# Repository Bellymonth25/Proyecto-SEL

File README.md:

# Proyecto-SEL
Proyecto del desarrollo de una PCB de un filtro paso bajas de 8vo orden.

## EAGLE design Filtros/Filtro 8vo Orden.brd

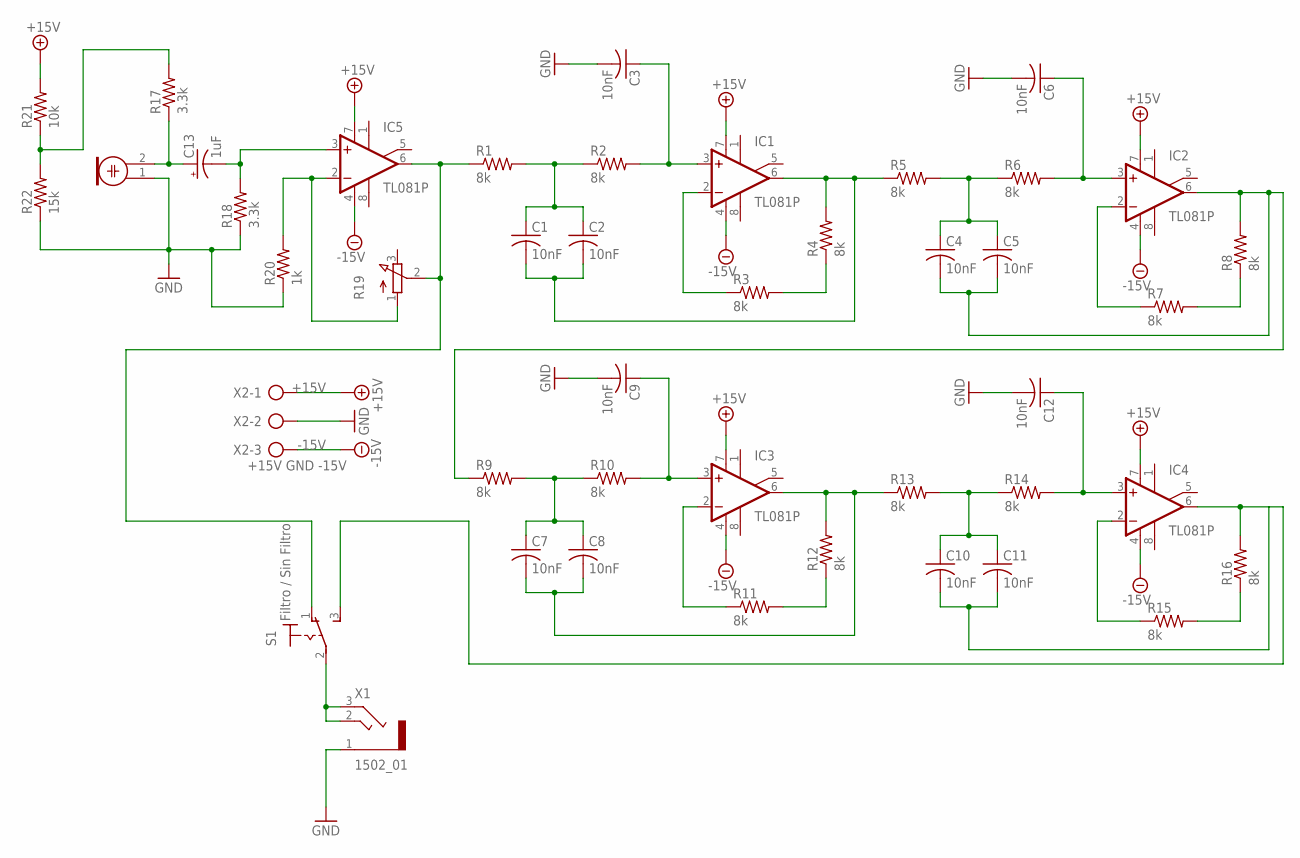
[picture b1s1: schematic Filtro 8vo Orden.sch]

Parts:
C1, C2, C3, C4, C5, C6, C7, C8, C9, C10, C11, C12: 10nF; C0805
C13: 1uF; E1,8-4
IC1, IC2, IC3, IC4, IC5: TL081P; DIL08
M1: ELECTRET_MICROPHONWM-63PR; WM-63PR
R1, R2, R3, R4, R5, R6, R7, R8, R9, R10, R11, R12, R13, R14, R15, R16: 8k; 0204/7
R17, R18: 3.3k; 0204/7
R19: 3RP/1610N
R20: 1k; 0204/7
R21: 10k; 0204/7
R22: 15k; 0204/7
S1: Filtro / Sin Filtro; 320-916
X1: 1502_01
X2: +15V GND -15V; AK300/3

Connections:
+15V: IC1.7 (V+), IC2.7 (V+), IC3.7 (V+), IC4.7 (V+), IC5.7 (V+), R21.2, X2.1
-15V: IC1.4 (V-), IC2.4 (V-), IC3.4 (V-), IC4.4 (V-), IC5.4 (V-), X2.3
GND: C3.2, C6.2, C9.2, C12.2, M1.1, R18.1, R20.1, R22.1, X1.1, X2.2
unnamed: C6.1, IC2.3 (+IN), R6.2
unnamed: C3.1, IC1.3 (+IN), R2.2
unnamed: R3.2, R4.1
unnamed: C4.1, C5.1, R5.2, R6.1
unnamed: C4.2, C5.2, IC2.6 (OUT), R8.2, R9.1
unnamed: C1.1, C2.1, R1.2, R2.1
unnamed: C1.2, C2.2, IC1.6 (OUT), R4.2, R5.1
unnamed: IC1.2 (-IN), R3.1
unnamed: IC2.2 (-IN), R7.1
unnamed: R7.2, R8.1
unnamed: C9.1, IC3.3 (+IN), R10.2
unnamed: C7.1, C8.1, R9.2, R10.1
unnamed: C7.2, C8.2, IC3.6 (OUT), R12.2, R13.1
unnamed: IC3.2 (-IN), R11.1
unnamed: R11.2, R12.1
unnamed: C12.1, IC4.3 (+IN), R14.2
unnamed: C10.1, C11.1, R13.2, R14.1
unnamed: C10.2, C11.2, IC4.6 (OUT), R16.2, S1.3 (S)
unnamed: IC4.2 (-IN), R15.1
unnamed: R15.2, R16.1
unnamed: C13.+, M1.2, R17.1
unnamed: C13.-, IC5.3 (+IN), R18.2
unnamed: R17.2, R21.1, R22.2
unnamed: IC5.2 (-IN), R19.1 (A), R20.2
unnamed: S1.2, X1.2 (3), X1.3 (2)
unnamed: IC5.6 (OUT), R1.1, R19.2 (S), S1.1 (O)

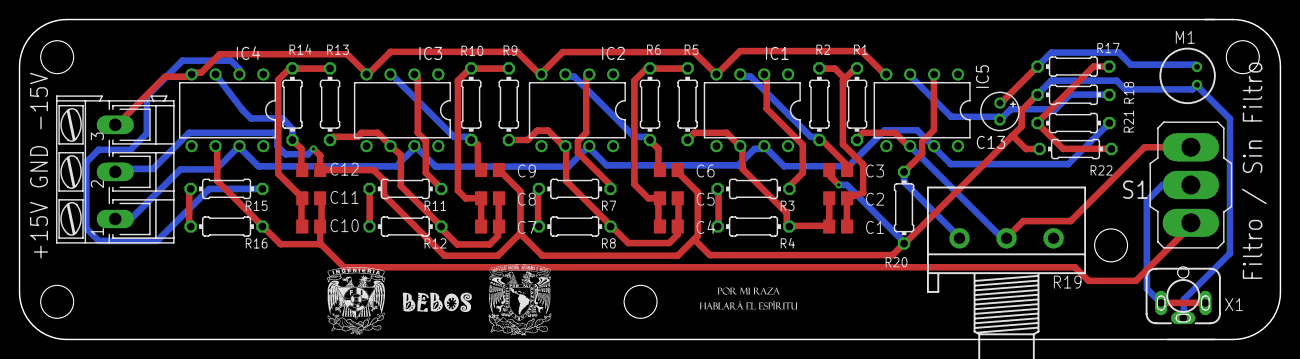
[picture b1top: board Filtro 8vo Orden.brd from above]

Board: 2 copper layers, 134.0 x 34.0 mm, 44 parts (0 on the bottom side), 29 nets.

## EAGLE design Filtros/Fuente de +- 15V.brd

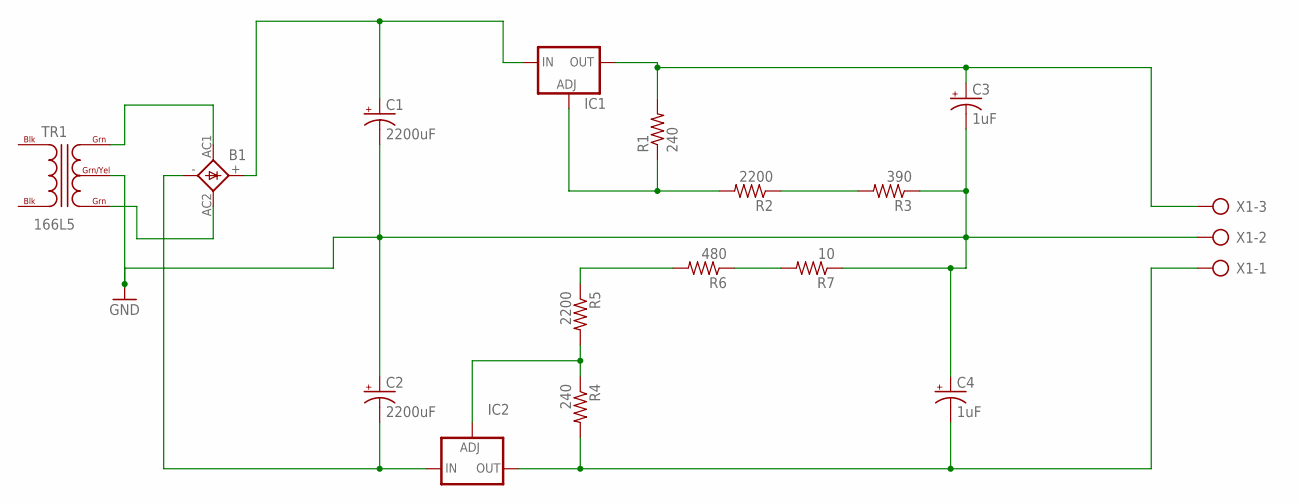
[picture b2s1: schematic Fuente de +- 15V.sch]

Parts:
B1: 2KBP
C1, C2: 2200uF; E7,5-16
C3, C4: 1uF; E1,8-4
IC1: LM317TS; 317TS
IC2: LM337TS; 337TS
R1, R4: 240; 0204/7
R2, R5: 2200; 0204/7
R3: 390; 0204/7
R6: 480; 0204/7
R7: 10; 0204/7
TR1: 166L5; C7H
X1: AK300/3

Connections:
GND: C1.-, C2.+, C3.-, C4.+, R3.1, R7.1, TR1.GRN/YEL, X1.2
unnamed: B1.AC1, TR1.GRN@1 (GRN)
unnamed: B1.AC2, TR1.GRN@2 (GRN)
unnamed: B1.+, C1.+, IC1.3 (IN)
unnamed: C3.+, IC1.2 (OUT), R1.2, X1.3
unnamed: C4.-, IC2.3 (OUT), R4.2, X1.1
unnamed: IC1.1 (ADJ), R1.1, R2.2
unnamed: R2.1, R3.2
unnamed: B1.-, C2.-, IC2.2 (IN)
unnamed: IC2.1 (ADJ), R4.1, R5.2
unnamed: R5.1, R6.2
unnamed: R6.1, R7.2

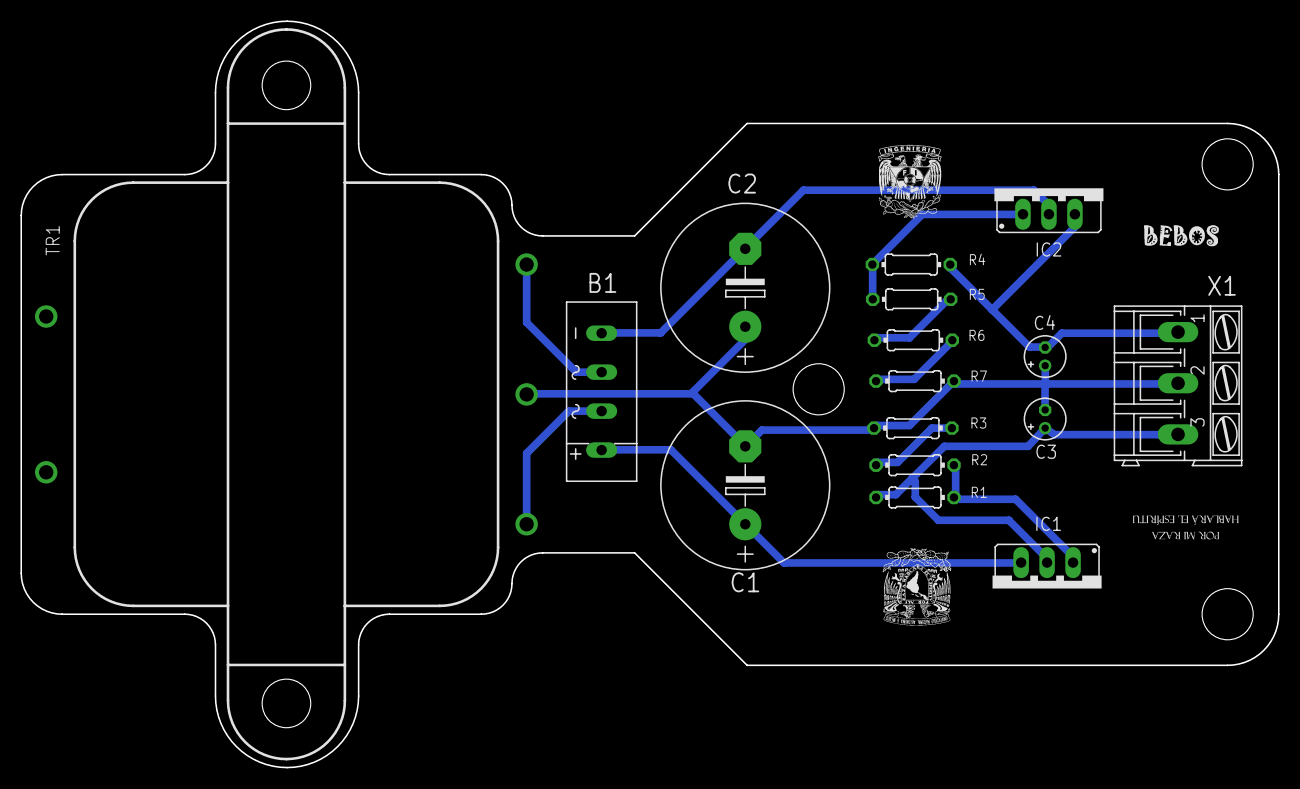
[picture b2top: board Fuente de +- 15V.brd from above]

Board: 2 copper layers, 123.0 x 73.0 mm, 16 parts (0 on the bottom side), 12 nets.

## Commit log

2022-01-07 Se agregaron algunos documentos
    Se agregaron los documentos:
    Filtros
    Fotos Cartel
    Modelos para Altspace VR
2022-01-07 Se agregaron más archivos
    Se agregaron:
    Modelos para Blender
    Texturas
    Archivos sueltos del proyecto
2022-01-07 Agregar modelos 3D
2022-01-07 Se agregaron modelos 3D
2022-01-07 Se agregaron los últimos modelos 3D
